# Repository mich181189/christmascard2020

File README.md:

# christmascard2020
I made a christmas card with WS2812B LEDs and it supports Micropython!

There is some HTML documentation generated from the /docs/ folder at https://mich181189.github.io/christmascard2020/index.html

The board is intended to run Micropython, a fork of which (with some additions to support this hardware) is available here: https://github.com/mich181189/christmascard2020_micropython

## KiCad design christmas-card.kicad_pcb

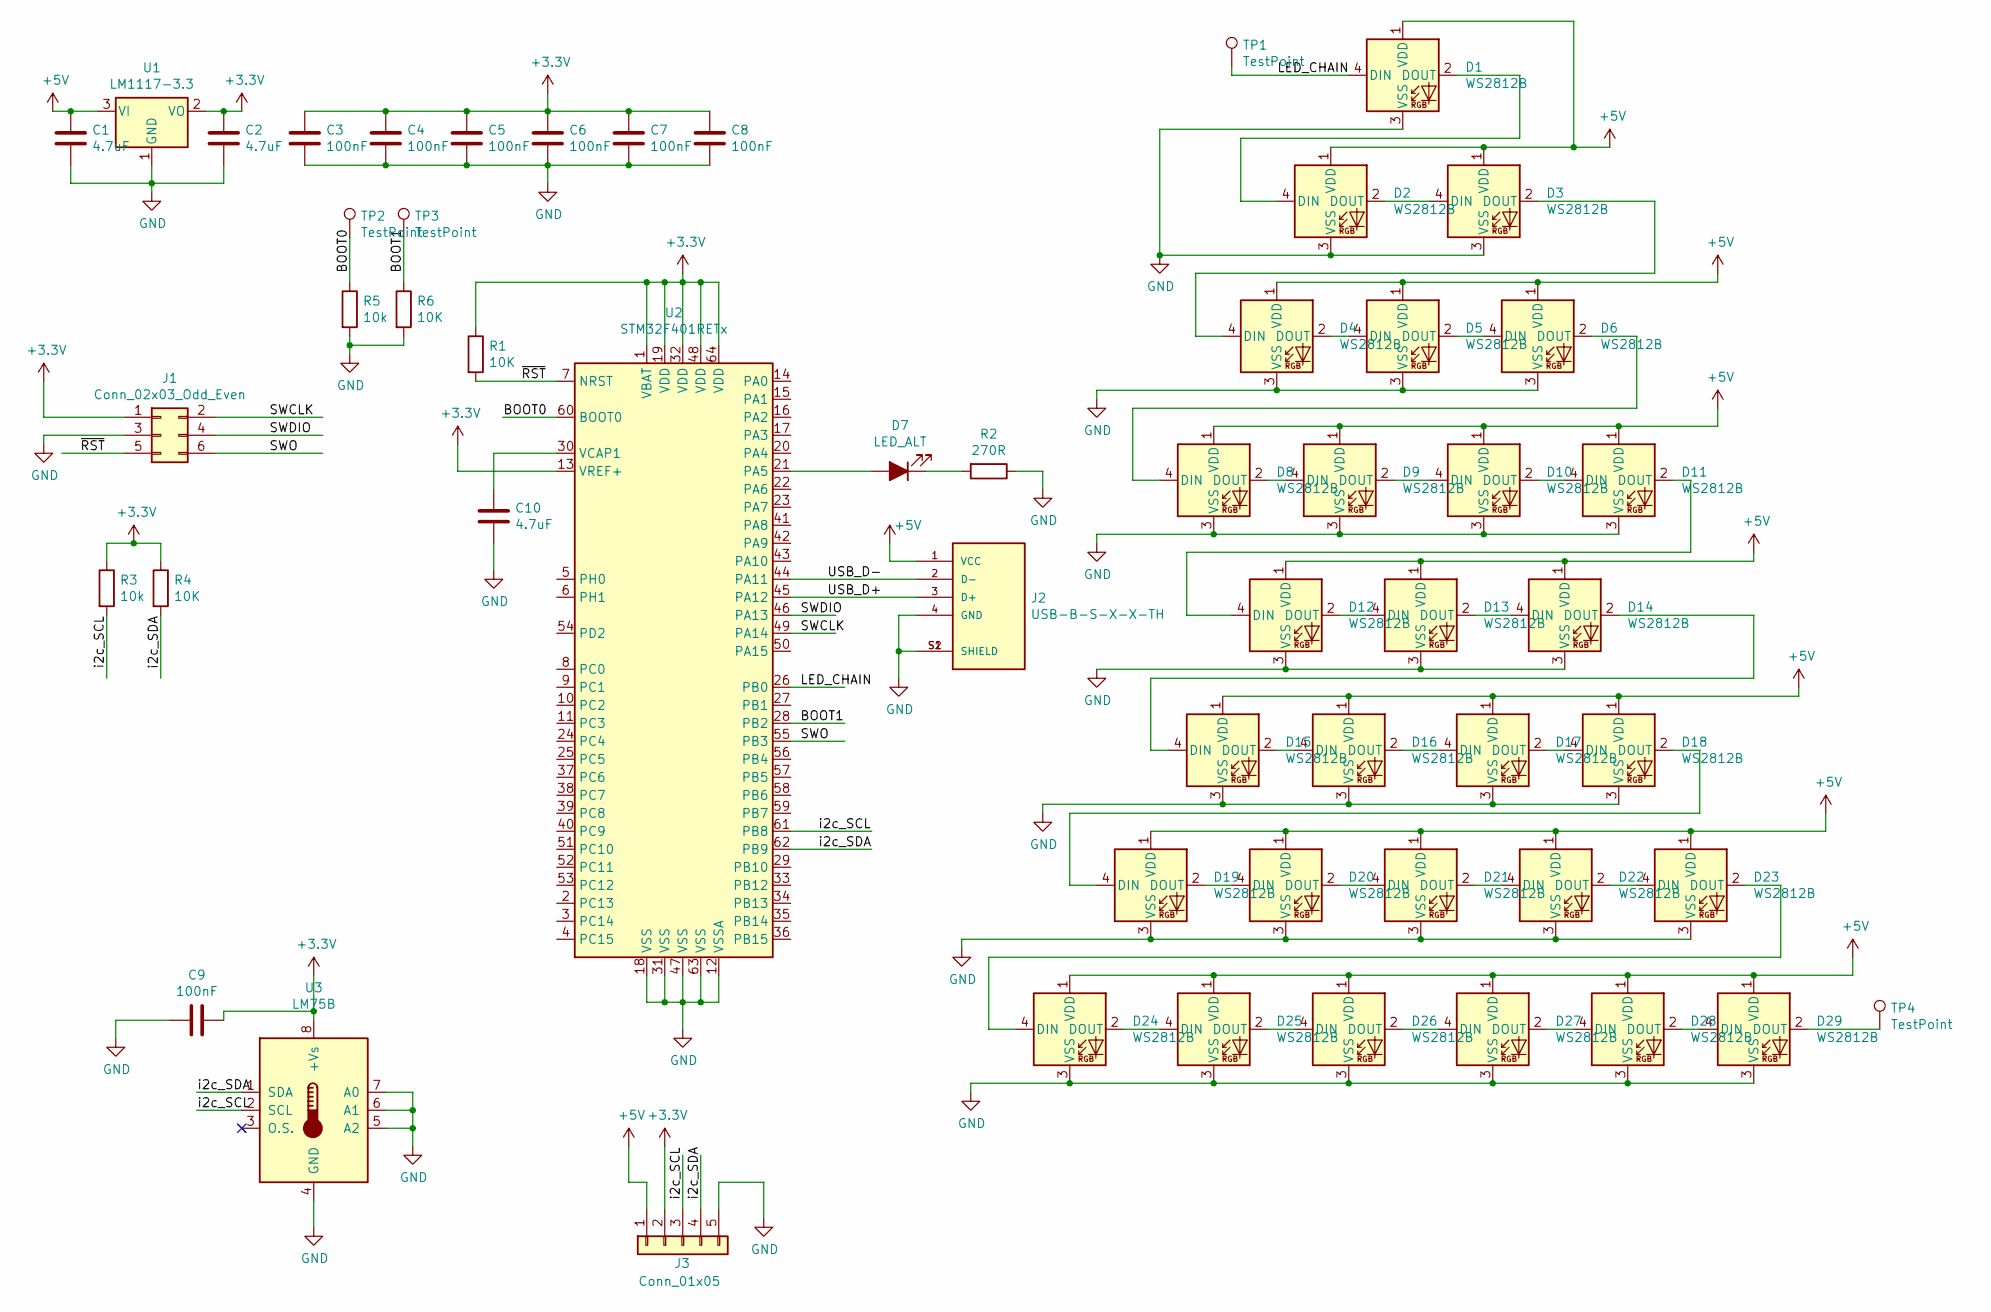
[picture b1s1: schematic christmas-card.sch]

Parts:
C1, C2, C10: 4.7uF; C_0805_2012Metric
C3, C4, C5, C6, C7, C8, C9: 100nF; C_0603_1608Metric
D1, D2, D3, D4, D5, D6, D8, D9, D10, D11, D12, D13, D14, D15, D16, D17, D18, D19, D20, D21, D22, D23, D24, D25, D26, D27, D28, D29: WS2812B; LED_WS2812B_PLCC4_5.0x5.0mm_P3.2mm
D7: LED_ALT; D_0805_2012Metric
J1: Conn_02x03_Odd_Even; TC2030-MCP-NL
J2: USB-B-S-X-X-TH; SAMTEC_USB-B-S-X-X-TH; PARTREV Q
J3: Conn_01x05; PinHeader_1x05_P2.54mm_Vertical
R1, R4, R6: 10K; R_0603_1608Metric
R2: 270R; R_0603_1608Metric
R3, R5: 10k; R_0603_1608Metric
TP1, TP4: TestPoint; TestPoint_Loop_D1.80mm_Drill1.0mm_Beaded
TP2, TP3: TestPoint; TestPoint_Pad_D1.0mm
U1: LM1117-3.3; SOT-223-3_TabPin2
U2: STM32F401RETx; LQFP-64_10x10mm_P0.5mm
U3: LM75B; SOIC-8_3.9x4.9mm_P1.27mm

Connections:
+3V3: C2.1, C3.1, C4.1, C5.1, C6.1, C7.1, C8.1, C9.1, J1.1, J3.2, R1.1, R3.1, R4.1, U1.2 (VO), U2.1 (VBAT), U2.13 (VREF+), U2.19 (VDD), U2.32 (VDD), U2.48 (VDD), U2.64 (VDD), U3.8 (+Vs)
+5V: C1.1, D1.1 (VDD), D2.1 (VDD), D3.1 (VDD), D4.1 (VDD), D5.1 (VDD), D6.1 (VDD), D8.1 (VDD), D9.1 (VDD), D10.1 (VDD), D11.1 (VDD), D12.1 (VDD), D13.1 (VDD), D14.1 (VDD), D15.1 (VDD), D16.1 (VDD), D17.1 (VDD), D18.1 (VDD), D19.1 (VDD), D20.1 (VDD), D21.1 (VDD), D22.1 (VDD), D23.1 (VDD), D24.1 (VDD), D25.1 (VDD), D26.1 (VDD), D27.1 (VDD), D28.1 (VDD), D29.1 (VDD), J2.1 (VCC), J3.1, U1.3 (VI)
/BOOT0: R5.1, TP2.1, U2.60 (BOOT0)
/BOOT1: R6.1, TP3.1, U2.28 (PB2)
/LED_CHAIN: D1.4 (DIN), TP1.1, U2.26 (PB0)
/SWCLK: J1.2, U2.49 (PA14)
/SWDIO: J1.4, U2.46 (PA13)
/SWO: J1.6, U2.55 (PB3)
/USB_D+: J2.3 (D+), U2.45 (PA12)
/USB_D-: J2.2 (D-), U2.44 (PA11)
/i2c_SCL: J3.3, R3.2, U2.61 (PB8), U3.2 (SCL)
/i2c_SDA: J3.4, R4.2, U2.62 (PB9), U3.1 (SDA)
/~RST: J1.5, R1.2, U2.7 (NRST)
GND: C1.2, C2.2, C3.2, C4.2, C5.2, C6.2, C7.2, C8.2, C9.2, C10.1, D1.3 (VSS), D2.3 (VSS), D3.3 (VSS), D4.3 (VSS), D5.3 (VSS), D6.3 (VSS), D8.3 (VSS), D9.3 (VSS), D10.3 (VSS), D11.3 (VSS), D12.3 (VSS), D13.3 (VSS), D14.3 (VSS), D15.3 (VSS), D16.3 (VSS), D17.3 (VSS), D18.3 (VSS), D19.3 (VSS), D20.3 (VSS), D21.3 (VSS), D22.3 (VSS), D23.3 (VSS), D24.3 (VSS), D25.3 (VSS), D26.3 (VSS), D27.3 (VSS), D28.3 (VSS), D29.3 (VSS), J1.3, J2.4 (GND), J2.S1 (SHIELD), J2.S2 (SHIELD), J3.5, R2.1, R5.2, R6.2, U1.1 (GND), U2.12 (VSSA), U2.18 (VSS), U2.31 (VSS), U2.47 (VSS), U2.63 (VSS), U3.4 (GND), U3.5 (A2), U3.6 (A1), U3.7 (A0)
unnamed: C10.2, U2.30 (VCAP1)
unnamed: D1.2 (DOUT), D2.4 (DIN)
unnamed: D2.2 (DOUT), D3.4 (DIN)
unnamed: D3.2 (DOUT), D4.4 (DIN)
unnamed: D4.2 (DOUT), D5.4 (DIN)
unnamed: D5.2 (DOUT), D6.4 (DIN)
unnamed: D6.2 (DOUT), D8.4 (DIN)
unnamed: D7.1 (K), R2.2
unnamed: D7.2 (A), U2.21 (PA5)
unnamed: D8.2 (DOUT), D9.4 (DIN)
unnamed: D10.2 (DOUT), D11.4 (DIN)
unnamed: D9.2 (DOUT), D10.4 (DIN)
unnamed: D11.2 (DOUT), D12.4 (DIN)
unnamed: D12.2 (DOUT), D13.4 (DIN)
unnamed: D13.2 (DOUT), D14.4 (DIN)
unnamed: D14.2 (DOUT), D15.4 (DIN)
unnamed: D15.2 (DOUT), D16.4 (DIN)
unnamed: D16.2 (DOUT), D17.4 (DIN)
unnamed: D17.2 (DOUT), D18.4 (DIN)
unnamed: D18.2 (DOUT), D19.4 (DIN)
unnamed: D19.2 (DOUT), D20.4 (DIN)
unnamed: D20.2 (DOUT), D21.4 (DIN)
unnamed: D21.2 (DOUT), D22.4 (DIN)
unnamed: D22.2 (DOUT), D23.4 (DIN)
unnamed: D23.2 (DOUT), D24.4 (DIN)
unnamed: D24.2 (DOUT), D25.4 (DIN)
unnamed: D25.2 (DOUT), D26.4 (DIN)
unnamed: D26.2 (DOUT), D27.4 (DIN)
unnamed: D27.2 (DOUT), D28.4 (DIN)
unnamed: D28.2 (DOUT), D29.4 (DIN)
unnamed: D29.2 (DOUT), TP4.1

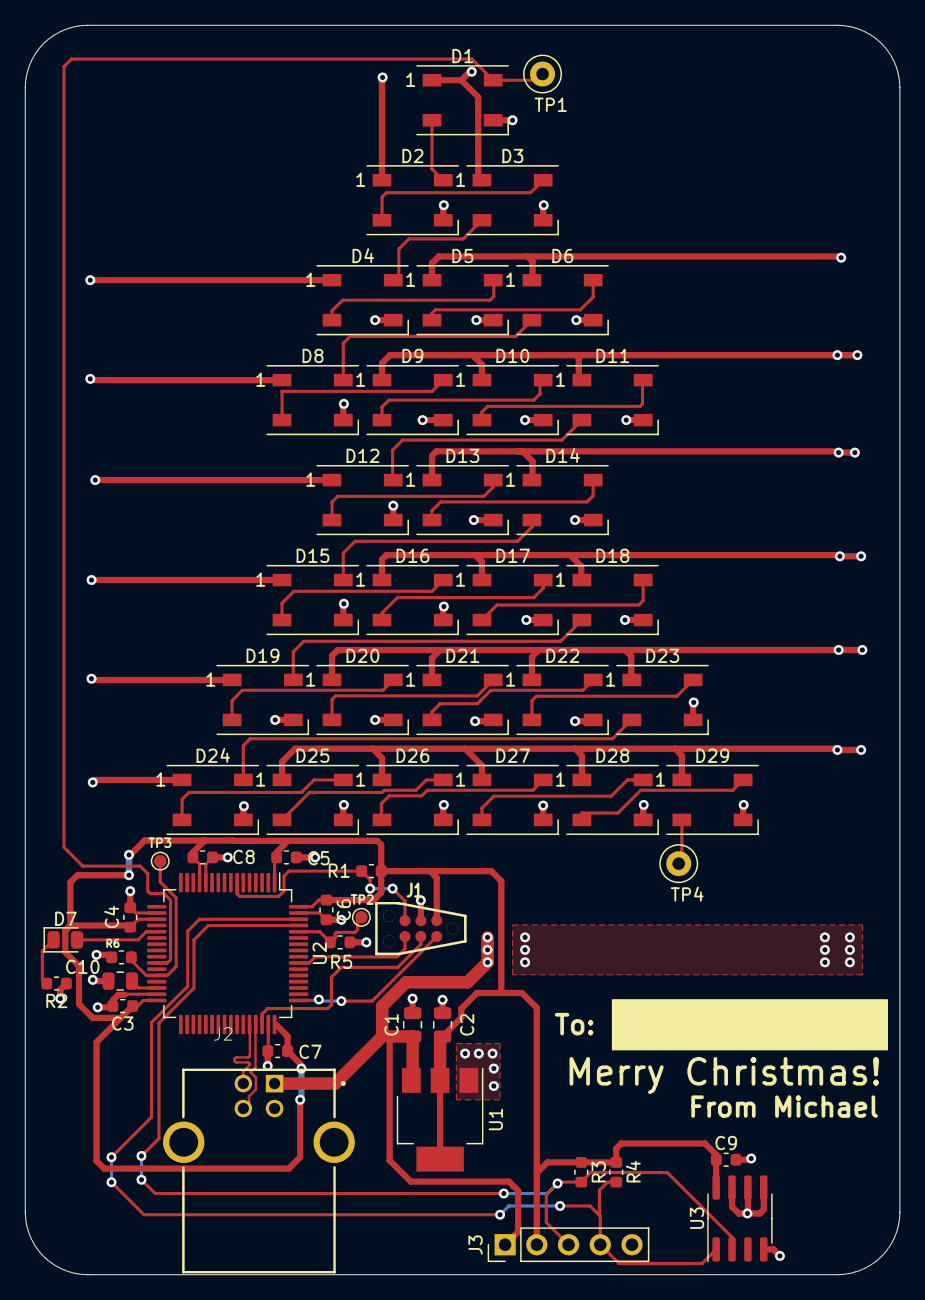
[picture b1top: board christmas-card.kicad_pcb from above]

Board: 2 copper layers, 70.0 x 100.0 mm, 55 parts (0 on the bottom side), 45 nets.

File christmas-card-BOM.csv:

Comment,Designator,Footprint,LCSC
4.7uF,"C1,C2,C10",Capacitor_SMD:C_0805_2012Metric,C1779
100nF,"C3,C4,C5,C6,C7,C8,C9",Capacitor_SMD:C_0603_1608Metric,C14663
WS2812B,"D1,D2,D3,D4,D5,D6,D8,D9,D10,D11,D12,D13,D14,D15,D16,D17,D18,D19,D20,D21,D22,D23,D24,D25,D26,D27,D28,D29",LED_SMD:LED_WS2812B_PLCC4_5.0x5.0mm_P3.2mm,C114586
LED_ALT,D7,Diode_SMD:D_0805_2012Metric,C84256
10K,"R1,R3,R4,R5,R6",Resistor_SMD:R_0603_1608Metric,C25804
270R,R2,Resistor_SMD:R_0603_1608Metric,C22966
AMS1117-3.3,U1,Package_TO_SOT_SMD:SOT-223-3_TabPin2,C6186
STM32F401RETx,U2,Package_QFP:LQFP-64_10x10mm_P0.5mm,C116978
LM75B,U3,Package_SO:SOIC-8_3.9x4.9mm_P1.27mm,C34565

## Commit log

2020-12-10 Added Schematic PDF
2020-12-14 Initial docs
2020-12-14 Add Travis CI config to build docs automatically
2020-12-14 A few tweaks
2020-12-14 Deploy mich181189/christmascard2020 to github.com/mich181189/christmascard2020.git:gh-pages
2020-12-14 hopefully fix docs
2020-12-17 Moar Docz
2020-12-17 More docs tweaks
2020-12-17 Added notes on flashing
